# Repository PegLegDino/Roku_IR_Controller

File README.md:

# Roku_Controller

This is a controller for the Roku
This software will provide you with both a template for sending and reciving IR signals as well as 
an example of the functional controller

I made this at 1AM so if none of this makes sense, I would be glad to answer questions you have in the issues tab...

# Quick_Setup_Guide
### Software_Requirements
* Processing IDE
* Install CP5 through processing
* Arduino IDE
* Install IRremote through arduino
### Hardware_Requirements
* Arduino Uno or any AVR microcontroller with at least 5kb EEPROM (5 kilo bytes storage so probably no TinyAVR series chips...Drop a comment if you want optimization idk)
* IR Trasmitter LED ~3v
* Arduino infrared reciever module
* Resistor (25ohms-330ohms) *Lower resitance == far; High Resistance == not far
* Your hardware your sexy beast *rawr* xD
### Getting Started
#### The Code
* Processing:
This is the easy part, you just need to open the processing <a href="Project Files/Processing Code/Arduino GUI.pde " target="_blank">here</a> ... it's just that easy, if you want to know how it works refer to this ControlP5 reference doc [https://sojamo.de/libraries/archive/controlP5-0-3-14/reference/index.htm] and this processing thing [https://processing.org/reference/libraries/serial/index.html] ya NERD
* Arduino Code:
Sorry in advance, this is the hard part. 

When your run the <a href="Project Files\Receiver Code\Receiver Code.ino" target="_blank">reciever script</a> and click your remote at it you'll get a code, the last 4 represent the user while the first 4 represent the data being sent. It'll look like this in the serial monitor...that is your code, use it to change mine.

Each roku is different so a little fiddling may be required.

In Short just take the raw data from your remote signal and replace the last four characters of my user data with yours in this <a href="Project Files/Manual_Control/Manual_Control.ino" target="_blank">script</a> 

#### The Hard
* Follow the pictures (bonus points if you DM me a picture of the PCB)

OOOOOOOOOH LOOK A SCHEMATIC...*wow*

BOOM ANOTHER ONE (Update, I meant Transmitter)

NOW JUST THE ENGINEERS...if you get this you deserve a cookie it's just an atmega328p serial programming circuit 

*BONUS PCB DESIGN* (For those whomst wish to be extra)

# ChangeLog

I don't make changes I make genius

*Added first stuff 4/25/2022

*Revised that stuff 4/25/2022

*Remebered I left out a lot of stuff 4/25/2022 (but later)

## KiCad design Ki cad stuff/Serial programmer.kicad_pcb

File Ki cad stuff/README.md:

# Micro-B-design

This repository contains the design files for the Micro-B development board.

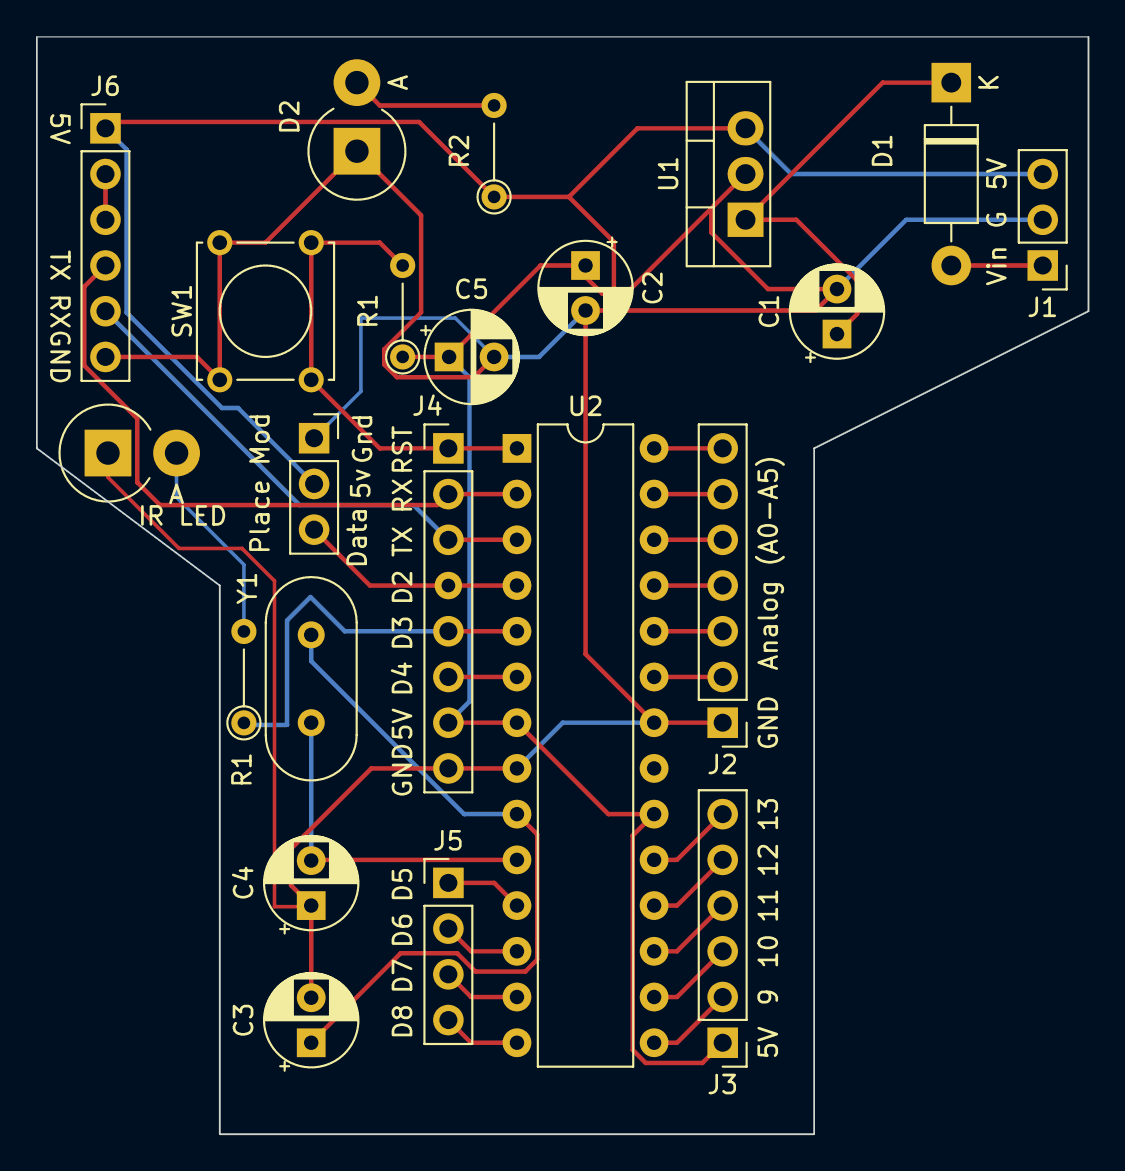
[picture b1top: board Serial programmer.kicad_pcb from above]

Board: 2 copper layers, 58.4 x 61.0 mm, 22 parts (0 on the bottom side), 29 nets.

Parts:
C1: 100u; CP_Radial_D5.0mm_P2.50mm
C2: 22u; CP_Radial_D5.0mm_P2.50mm
C3, C4: 22p; CP_Radial_D5.0mm_P2.50mm
C5: C; CP_Radial_D5.0mm_P2.50mm
D1: 1N4007; D_DO-41_SOD81_P10.16mm_Horizontal
D2: LED_ALT; D_DO-201_P3.81mm_Vertical_AnodeUp
IR LED: LED_ALT; D_DO-201_P3.81mm_Vertical_AnodeUp
J1: Conn_01x03_Male; PinHeader_1x03_P2.54mm_Vertical
J2: Conn_01x07_Female; PinHeader_1x07_P2.54mm_Vertical
J3, J6: Conn_01x06_Female; PinHeader_1x06_P2.54mm_Vertical
J4: Conn_01x08_Female; PinHeader_1x08_P2.54mm_Vertical
J5: Conn_01x04_Female; PinHeader_1x04_P2.54mm_Vertical
Place Mod: PinSocket_1x03_P2.54mm_Vertical
R1, R1#2: R; R_Axial_DIN0204_L3.6mm_D1.6mm_P5.08mm_Vertical
R2: 220; R_Axial_DIN0204_L3.6mm_D1.6mm_P5.08mm_Vertical
SW1: SW_Push; SW_Tactile_Straight_KSA0Axx1LFTR
U1: LM7805_TO220; TO-220-3_Vertical
U2: ATmega328P-PU; DIP-28_W7.62mm
Y1: Crystal; Crystal_HC49-U_Vertical

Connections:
+5V: C2.1, C5.1, J1.3, J3.1, J4.7, J6.1, R1.1, R2.1, U1.3, U2.7, U2.20
D5: J5.1, U2.11
D6: J5.2, U2.12
D8: J5.4, U2.14
GND: C1.2, C2.2, C3.2, C4.1, C5.2, D2.1, J1.2, J2.1, J4.8, J6.6, SW1.1, U1.2, U2.8, U2.22
MISO: J3.5, U2.18
MOSI: J3.4, U2.17
unnamed: C1.1, D1.1, U1.1
unnamed: D1.2, J1.1
unnamed: D2.2, R2.2
unnamed: J2.2, U2.23
unnamed: J2.3, U2.24
unnamed: J2.4, U2.25
unnamed: J2.5, U2.26
unnamed: J2.6, U2.27
unnamed: J2.7, U2.28
unnamed: J3.2, U2.15
unnamed: J3.3, U2.16
unnamed: J4.4, U2.4
unnamed: J4.5, U2.5
unnamed: J4.6, U2.6
unnamed: J5.3, U2.13
unnamed: J6.2, J6.3
RESET: J4.1, R1.2, SW1.2, U2.1
RX: J4.2, J6.4, U2.2
SCK: J3.6, U2.19
TX: J4.3, J6.5, U2.3
XTAL1: C3.1, U2.9, Y1.2
XTAL2: C4.2, U2.10, Y1.1

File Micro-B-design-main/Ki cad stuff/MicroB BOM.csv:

"Id";"Designator";"Package";"Quantity";"Designation";"Supplier and ref";
1;"J3,J6";"PinHeader_1x06_P2.54mm_Vertical";2;"Conn_01x06_Female";;;
2;"U2";"DIP-28_W7.62mm";1;"ATmega328P-PU";;;
3;"J1";"PinHeader_1x03_P2.54mm_Vertical";1;"Conn_01x03_Male";;;
4;"J5";"PinHeader_1x04_P2.54mm_Vertical";1;"Conn_01x04_Female";;;
5;"J4";"PinHeader_1x08_P2.54mm_Vertical";1;"Conn_01x08_Female";;;
6;"J2";"PinHeader_1x07_P2.54mm_Vertical";1;"Conn_01x07_Female";;;
7;"Y1";"Crystal_HC49-U_Vertical";1;"Crystal";;;
8;"U1";"TO-220-3_Vertical";1;"LM7805_TO220";;;
9;"SW1";"SW_Tactile_Straight_KSA0Axx1LFTR";1;"SW_Push";;;
10;"R2";"R_Axial_DIN0204_L3.6mm_D1.6mm_P5.08mm_Vertical";1;"220";;;
11;"R1";"R_Axial_DIN0204_L3.6mm_D1.6mm_P5.08mm_Vertical";1;"R";;;
12;"D2";"D_DO-201_P3.81mm_Vertical_AnodeUp";1;"LED_ALT";;;
13;"D1";"D_DO-41_SOD81_P10.16mm_Horizontal";1;"1N4007";;;
14;"C5";"CP_Radial_D5.0mm_P2.50mm";1;"C";;;
15;"C4,C3";"CP_Radial_D5.0mm_P2.50mm";2;"22p";;;
16;"C2";"CP_Radial_D5.0mm_P2.50mm";1;"22u";;;
17;"C1";"CP_Radial_D5.0mm_P2.50mm";1;"100u";;;

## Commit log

2022-04-25 First Schem added
2022-04-25 Rename MicroB.svg to Schematics.svg
